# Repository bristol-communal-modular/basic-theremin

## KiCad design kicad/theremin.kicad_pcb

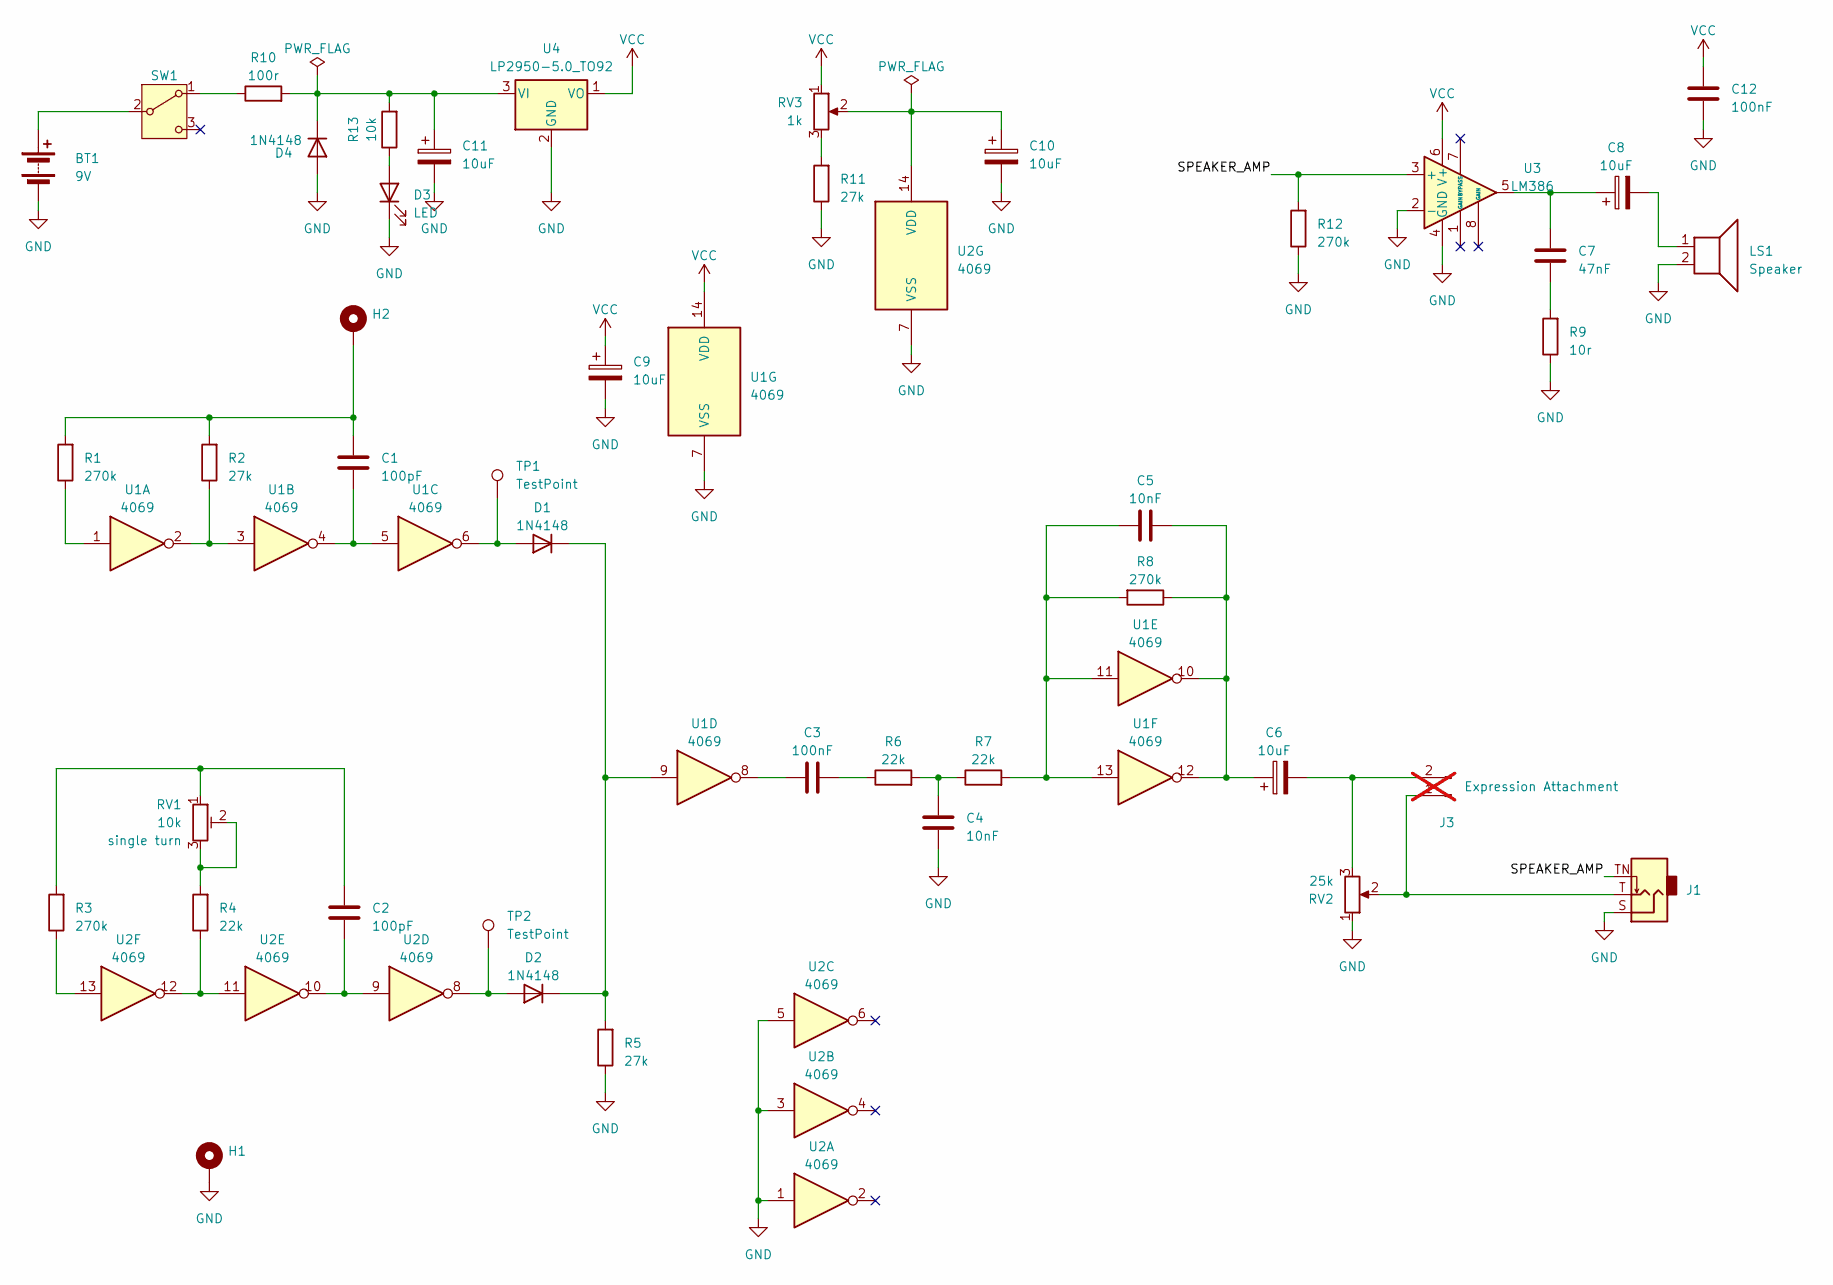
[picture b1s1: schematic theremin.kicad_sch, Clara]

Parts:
BT1: 9V; BatteryHolder_Eagle_12BH611-GRMODDEDBYROBIN
C1, C2: 100pF; C_Rect_L7.0mm_W3.5mm_P5.00mm; Tolerance 1%
C3, C12: 100nF; C_Rect_L7.0mm_W3.5mm_P5.00mm; Tolerance 5%
C4, C5: 10nF; C_Rect_L7.0mm_W3.5mm_P5.00mm; Tolerance 5%
C6, C8, C9, C10, C11: 10uF; CP_Radial_D5.0mm_P2.50mm; Tolerance 20%; Voltage 50v
C7: 47nF; C_Rect_L7.0mm_W3.5mm_P5.00mm; Tolerance 5%
D1, D2, D4: 1N4148; D_DO-35_SOD27_P7.62mm_Horizontal
D3: LED; LED_D5.0mm
H1, H2: MountingHole_Pad; crocclipcircleee
J1: Eurorack Mono Jack; Jack_3.5mm_QingPu_WQP-PJ398SM_Vertical; mpn WQP-WQP518MA
J3: Expression Attachment; PinHeader_1x02_P2.54mm_Vertical; not fitted
LS1: Speaker; 40mmSpeakerdropin
R1, R3, R8, R12: 270k; R_Axial_DIN0207_L6.3mm_D2.5mm_P10.16mm_Horizontal; Tolerance 1%
R2, R5, R11: 27k; R_Axial_DIN0207_L6.3mm_D2.5mm_P10.16mm_Horizontal; Tolerance 1%
R4, R6, R7: 22k; R_Axial_DIN0207_L6.3mm_D2.5mm_P10.16mm_Horizontal; Tolerance 1%
R9: 10r; R_Axial_DIN0207_L6.3mm_D2.5mm_P10.16mm_Horizontal; Tolerance 1%
R10: 100r; R_Axial_DIN0207_L6.3mm_D2.5mm_P10.16mm_Horizontal; Tolerance 1%
R13: 10k; R_Axial_DIN0207_L6.3mm_D2.5mm_P10.16mm_Horizontal; Tolerance 1%
RV1: 10k; Potentiometer_THT_Bourns_3306P_Vertical
RV2: 25k; Potentiometer_Alpha_RD901F-40-00D_Single_Vertical
RV3: 1k; Potentiometer_Alpha_RD901F-40-00D_Single_Vertical
SW1: SW_SPDT; SW_Slide_SPDT_Angled_CK_OS102011MA1Q
TP1, TP2: TestPoint; TestPoint_Loop_D2.50mm_Drill1.0mm_LowProfile
U1, U2: 4069; DIP-14_W7.62mm_Socket_LongPads
U3: LM386; DIP-8_W7.62mm_Socket_LongPads
U4: LP2950-5.0_TO92; TO-92_Inline_Wide

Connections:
/SPEAKER_AMP: J1.TN, R12.2, U3.3 (+)
GND: BT1.2 (-), C4.1, C9.2, C10.2, C11.2, C12.2, D3.1 (K), D4.2 (A), H1.1, J1.S, LS1.2, R5.1, R9.1, R11.1, R12.1, RV2.1, U1.7 (VSS), U2.1, U2.3, U2.5, U2.7 (VSS), U3.2 (-), U3.4 (GND), U4.2 (GND)
unnamed: BT1.1 (+), SW1.2 (B)
unnamed: C1.1, U1.4, U1.5
unnamed: C1.2, H2.1, R1.2, R2.2
unnamed: C2.1, U2.9, U2.10
unnamed: C2.2, R3.2, RV1.1
unnamed: C3.1, U1.8
unnamed: C3.2, R6.1
unnamed: C4.2, R6.2, R7.1
unnamed: C5.1, C6.1, R8.1, U1.10, U1.12
unnamed: C5.2, R7.2, R8.2, U1.11, U1.13
unnamed: C7.1, R9.2
unnamed: C7.2, C8.1, U3.5
unnamed: C8.2, LS1.1
unnamed: D1.2 (A), TP1.1, U1.6
unnamed: D1.1 (K), D2.1 (K), R5.2, U1.9
unnamed: D2.2 (A), TP2.1, U2.8
unnamed: D3.2 (A), R13.1
unnamed: C11.1, D4.1 (K), R10.2, R13.2, U4.3 (VI)
unnamed: J1.T, J3.1, RV2.2
unnamed: C6.2, J3.2, RV2.3
unnamed: R1.1, U1.1
unnamed: R2.1, U1.2, U1.3
unnamed: R3.1, U2.13
unnamed: R4.1, U2.11, U2.12
unnamed: R4.2, RV1.2, RV1.3
unnamed: R11.2, RV3.3
unnamed: R10.1, SW1.1 (A)
unnamed: C10.1, RV3.2, U2.14 (VDD)
VCC: C9.1, C12.1, RV3.1, U1.14 (VDD), U3.6 (V+), U4.1 (VO)

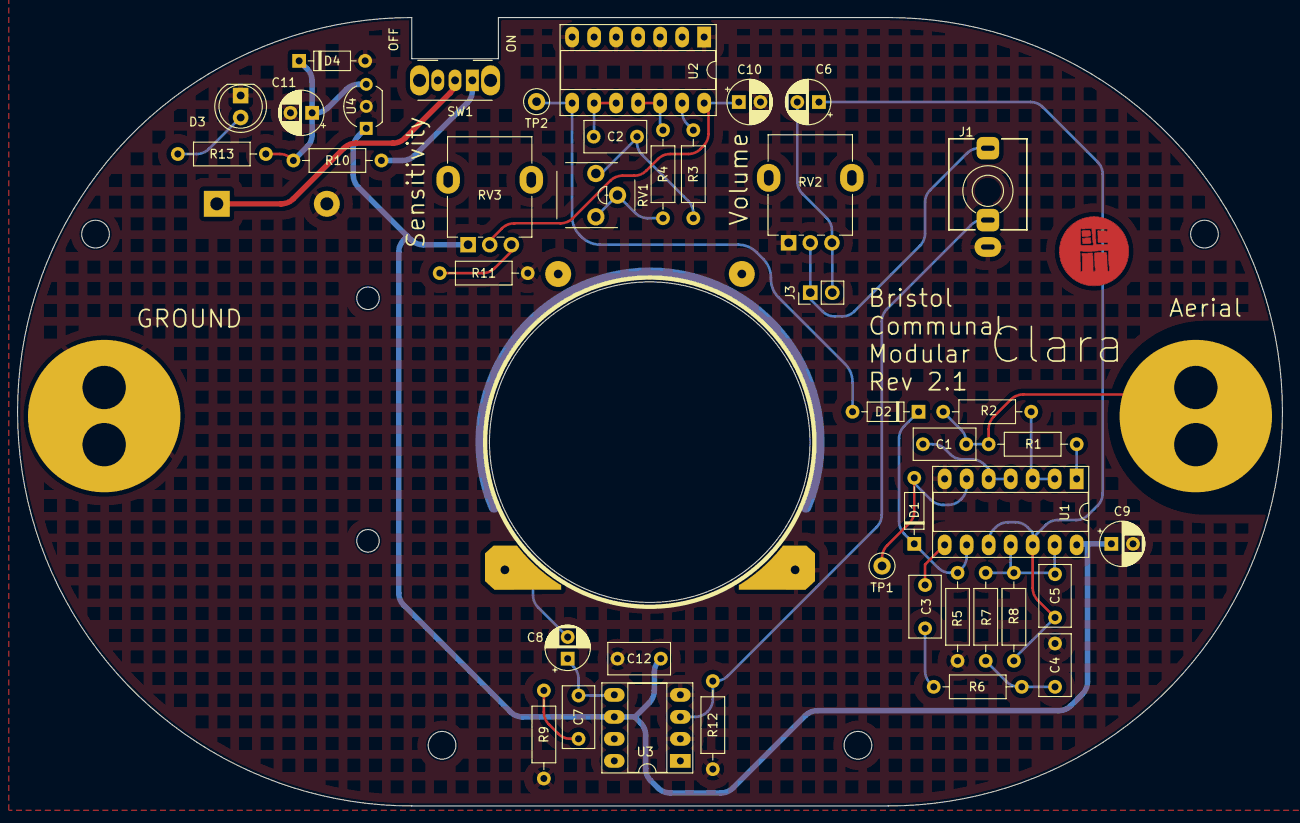
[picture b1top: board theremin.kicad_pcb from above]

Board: 2 copper layers, 146.0 x 91.0 mm, 49 parts (1 on the bottom side), 31 nets.

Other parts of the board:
EF**: MountingHole_3.2mm_M3
EF**#2, EF**#3, EF**#4: MountingHole_3.2mm_M3

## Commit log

2024-06-19 Updating with new footprints and some tweaks
2024-06-30 Now with extra pretty!
    Added the updated prettiefied version of the theremin files and added some quality of life features such as battery clip, crocodile clip friendly connectors, built in speaker & a power switch
2024-07-02 Tidying things up a bit
2024-07-03 More updates
2024-07-03 More tweaks
2024-07-03 Regenerating gerbers
2024-07-04 Final tweaks to make sure the front plate holes are on grid
2024-07-22 Adding interactive bom
2024-09-18 Fixing issues with layout
    * Making sure speaker fixing copper isn't covered on speaker footprint
    * Adding two more plated holes to make fixing speaker easier
    * Making holes for battery holder smaller so easier to solder
    * Adding another mounting hole for faceplate
    * Tweaking value and reference text placements
2024-09-18 Adding schematic page text
2024-09-18 Adding updated gerbers
2024-09-18 Adding schematic to build directory
2024-09-18 Updating interactive bom
2024-09-18 Adding testpoints at output of oscillators
2024-09-18 Updating schematic
2024-09-18 Creating BOM as csv and pdf files
2024-09-18 Adding parts placement guides
2024-09-22 Updating correct LED resistor value

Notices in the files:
kicad/theremin.kicad_pcb:
creativecommons.org/licenses/by/4.0
License: CC BY 4.0
